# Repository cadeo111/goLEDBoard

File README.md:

# Go LED board
this project is to create a [Go](https://en.wikipedia.org/wiki/Go_(game)) 
game board made out of LEDs so that you can play go on the go

The plan is to use a an ATSAMD51 microcontroller 
to drive an array of individually address able "neopixel" WS2812 LEDs 

the first version will be a 9x9 LED matrix, with plans for a full scale one afterwards

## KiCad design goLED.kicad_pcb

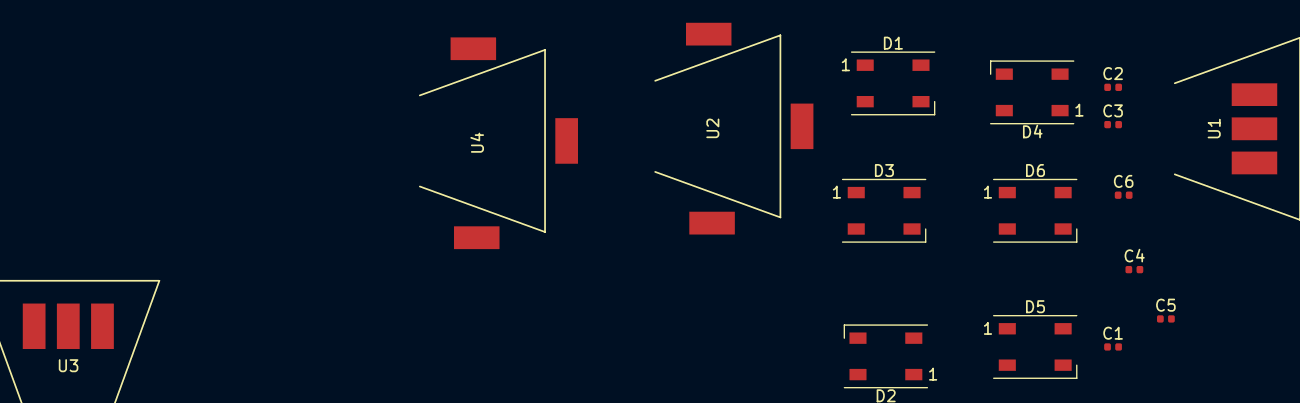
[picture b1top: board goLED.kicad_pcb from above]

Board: 2 copper layers, 16 parts (0 on the bottom side), 12 nets, no tracks yet.

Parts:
C1, C2, C3, C4, C5, C6: 0.1µF; C_0402_1005Metric
D1, D2, D3, D4, D5, D6: WS2812B; LED_WS2812B_PLCC4_5.0x5.0mm_P3.2mm
U1, U3: S_CON_M
U2, U4: S_CON_F

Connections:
+5V: C1.1, C2.1, C3.1, C4.1, C5.1, C6.1, D1.1, D2.1, D3.1, D4.1, D5.1, D6.1, U1.1, U2.1
/LED_single/DIN: D1.4, U1.3
/sheet5BA086B9/DIN: D4.4, D5.2
/sheet5BA086B9/DOUT: D4.2, U2.3
/sheet5BA086BA/DIN: D5.4, D6.2
/sheet5BA086BB/DIN: D3.2, D6.4
/sheet5BA0862F/DIN: D1.2, D2.4
/sheet5BA0863D/DIN: D2.2, D3.4
GND: C1.2, C2.2, C3.2, C4.2, C5.2, C6.2, D1.3, D2.3, D3.3, D4.3, D5.3, D6.3, U1.2, U2.2
unnamed: U3.1, U4.1
unnamed: U3.2, U4.2
unnamed: U3.3, U4.3

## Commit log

2020-07-26 finished for the most part
